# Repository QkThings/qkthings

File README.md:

Welcome to QkThings!
=====================

The open source framework and modular platform for smart devices.

**IMPORTANT:** read the [Building Instructions](http://discourse.qkthings.com/t/building-instructions/20) before cloning this repository.

Questions? Bugs? Visit [community.qkthings.com](http://community.qkthings.com) or send an email to `hello@qkthings.com`

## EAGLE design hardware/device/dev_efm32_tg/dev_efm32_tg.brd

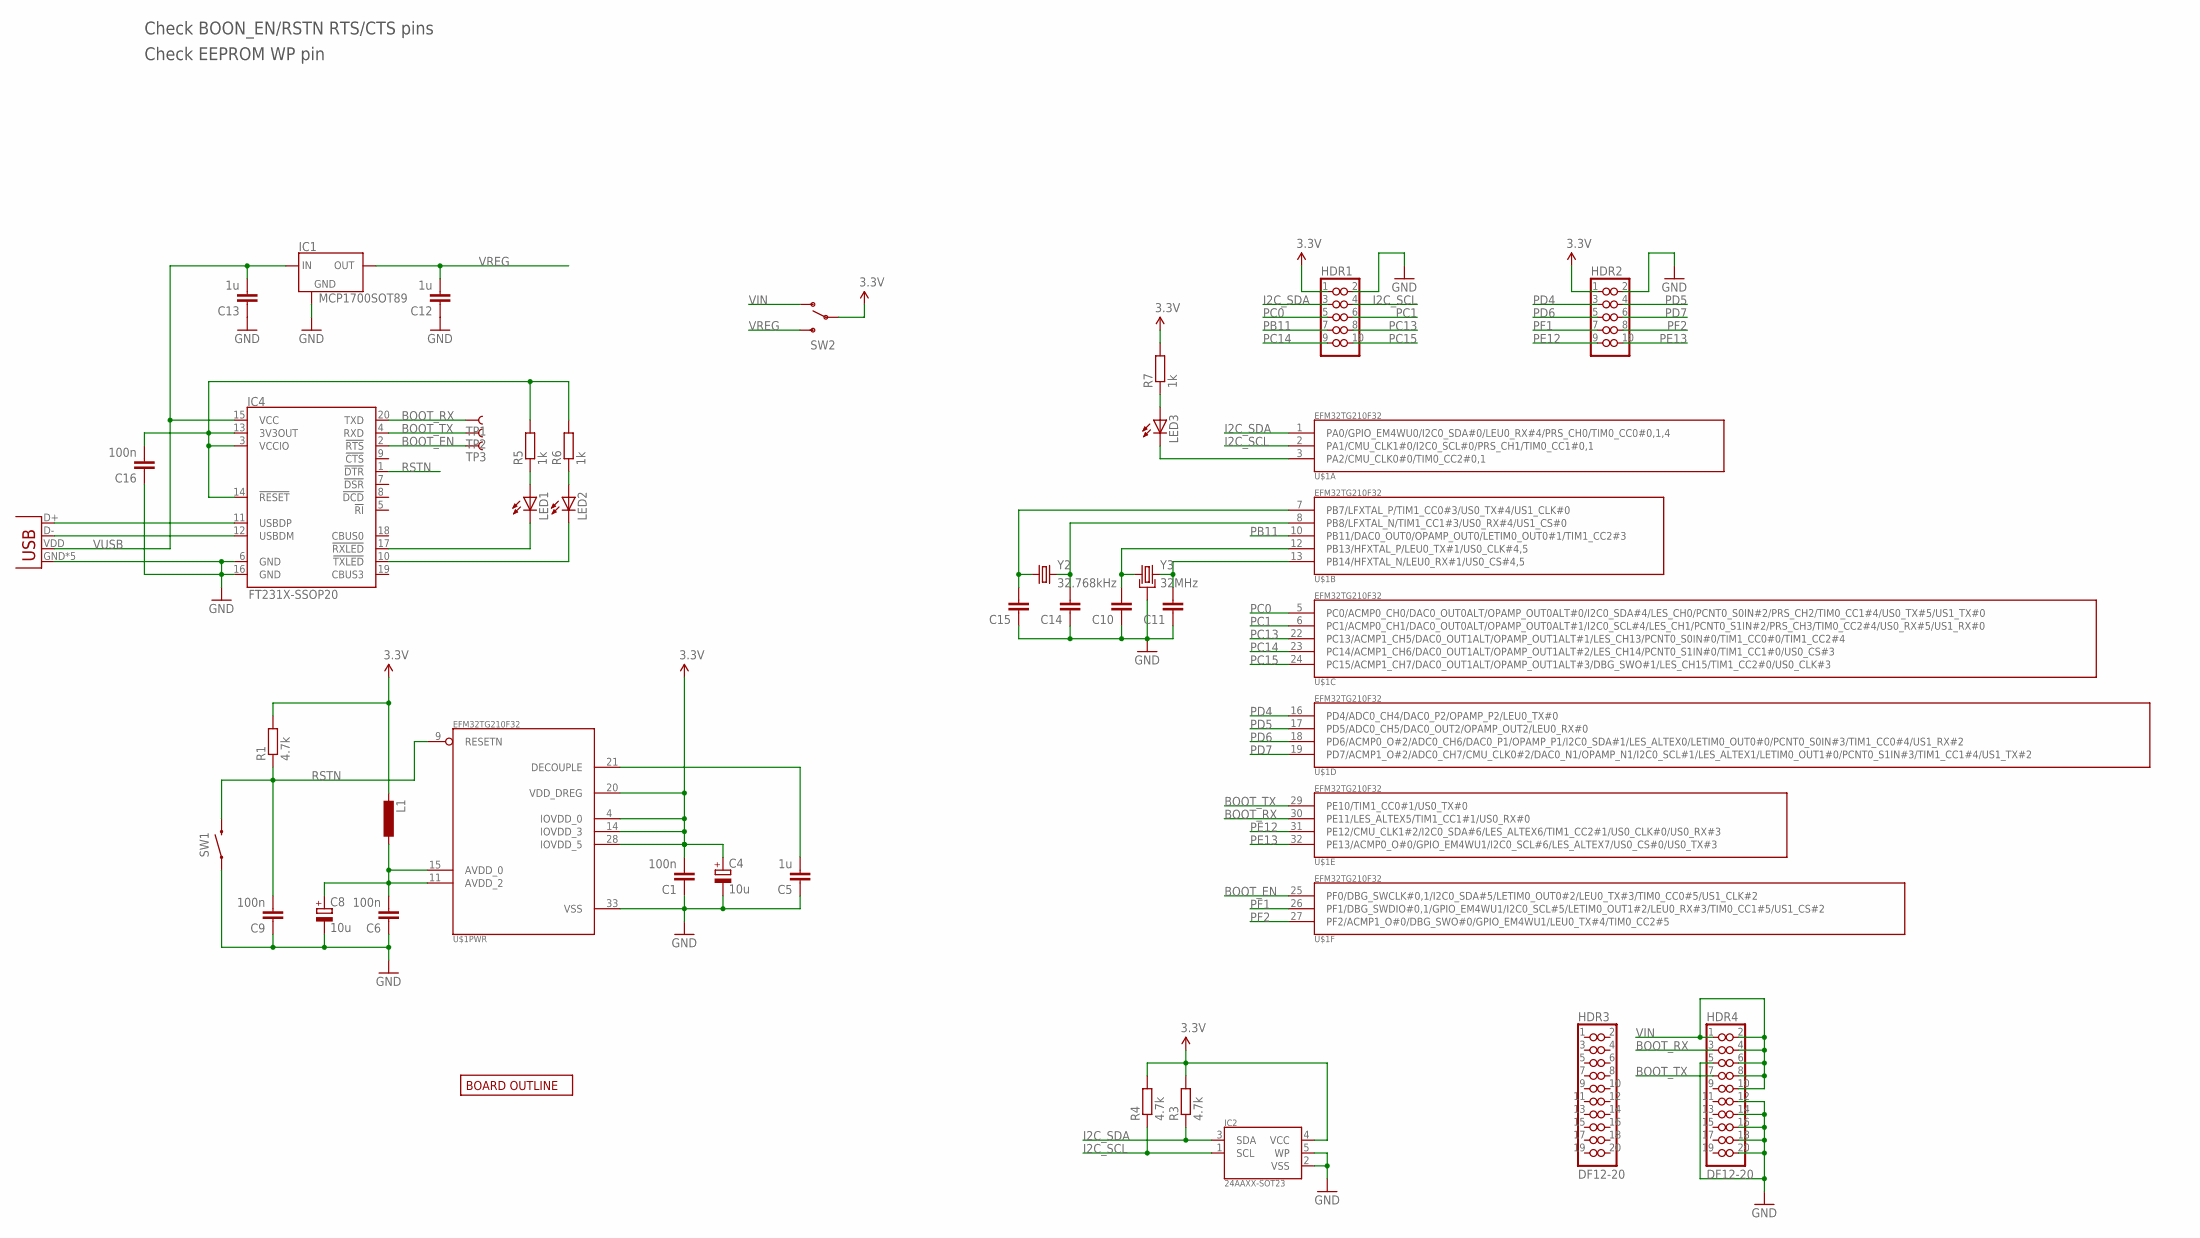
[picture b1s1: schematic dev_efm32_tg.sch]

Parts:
C1, C6, C9, C16: 100n; 0402
C4, C8: 10u; CAP_CASE_A
C5, C12, C13: 1u; 0402
C10, C11, C14, C15: C-0402; 0402
HDR1, HDR2: HDR2X05-ROUND; 2X05ROUND
HDR3, HDR4: DF12-20; DF12_20_MF
IC1: MCP1700SOT89; SOT89
IC2: 24AAXX-SOT23; SOT23-5
IC4: FT231X-SSOP20; SSOP20
L1: L-0402; 0402
LED1, LED2, LED3: LED0603; LED-0603
R1, R3, R4: 4.7k; 0402
R5, R6, R7: 1k; 0402
SW1: SWITCH_TACTILE-B3U-1000P; B3U-1000P
SW2: SWITCH_SPDT-PCM; PCM12SMTR
TP1, TP2, TP3: TP_1X1-1; TP_1X1_1
U$1: EFM32TG210F32; QFN32
U$2: USB-MICRO; 10118194_0001LF
U$3: QK-OUTLINE
Y2: 32.768kHz; ABS07
Y3: 32MHz; ABM8G

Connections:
3.3V: C1.2, C4.1 (+), HDR1.1, HDR2.1, IC2.4 (VCC), L1.2, R1.2, R3.2, R4.2, R7.2, SW2.2 (COM), U$1.4 (IOVDD_0), U$1.14 (IOVDD_3), U$1.20 (VDD_DREG), U$1.28 (IOVDD_5)
AVDD: C6.2, C8.1 (+), L1.1, U$1.11 (AVDD_2), U$1.15 (AVDD_0)
BOOT_EN: IC4.2 (!RTS), TP3.P$1, U$1.25 (PF0/DBG_SWCLK#0,1/I2C0_SDA#5/LETIM0_OUT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)
BOOT_RX: HDR4.3, IC4.20 (TXD), TP1.P$1, U$1.30 (PE11/LES_ALTEX5/TIM1_CC1#1/US0_RX#0)
BOOT_TX: HDR4.7, IC4.4 (RXD), TP2.P$1, U$1.29 (PE10/TIM1_CC0#1/US0_TX#0)
GND: C1.1, C4.2 (-), C5.1, C6.1, C8.2 (-), C9.1, C10.1, C11.1, C12.1, C13.1, C14.1, C15.1, C16.1, HDR1.2, HDR2.2, HDR4.5, HDR4.12, HDR4.14, HDR4.16, HDR4.18, HDR4.20, IC1.1 (GND), IC2.2 (VSS), IC2.5 (WP), IC4.6 (GND), IC4.16 (GND), SW1.P$1 (1), U$1.33 (VSS), U$2.GND, U$2.PAD1 (GND), U$2.PAD2 (GND), U$2.SHIELD1 (GND), U$2.SHIELD2 (GND), Y3.2 (SHIELD), Y3.4 (SHIELD)
I2C_SCL: HDR1.4, IC2.1 (SCL), R4.1, U$1.2 (PA1/CMU_CLK1#0/I2C0_SCL#0/PRS_CH1/TIM0_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)
I2C_SDA: HDR1.3, IC2.3 (SDA), R3.1, U$1.1 (PA0/GPIO_EM4WU0/I2C0_SDA#0/LEU0_RX#4/PR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)
unnamed: C5.2, U$1.21 (DECOUPLE)
unnamed: C11.2, U$1.13 (PB14/HFXTAL_N/LEU0_RX#1/US0_CS#4,5), Y3.3 (2)
unnamed: C14.2, U$1.8 (PB8/LFXTAL_N/TIM1_CC1#3/US0_RX#4/US1_CS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), Y2.P$2 (2)
unnamed: C10.2, U$1.12 (PB13/HFXTAL_P/LEU0_TX#1/US0_CLK#4,5), Y3.1
unnamed: C15.2, U$1.7 (PB7/LFXTAL_P/TIM1_CC0#3/US0_TX#4/US1_CL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), Y2.P$1 (1)
unnamed: IC4.11 (USBDP), U$2.D+
unnamed: IC4.12 (USBDM), U$2.D-
unnamed: LED1.A, R5.1
unnamed: LED2.A, R6.1
unnamed: IC4.17 (!RXLED), LED1.C
unnamed: IC4.10 (!TXLED), LED2.C
unnamed: LED3.A, R7.1
unnamed: LED3.C, U$1.3 (PA2/CMU_CLK0#0/TIM0_CC2#0,1)
unnamed: C16.2, IC4.3 (VCCIO), IC4.13 (3V3OUT), IC4.14 (!RESET), R5.2, R6.2
PB11: HDR1.7, U$1.10 (PB11/DAC0_OUT0/OPAMP_OUT0/LETIM0_OUT0#1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)
PC0: HDR1.5, U$1.5 (PC0/ACMP0_CH0/DAC0_OUT0ALT/OPAMP_OUT0AL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)
PC1: HDR1.6, U$1.6 (PC1/ACMP0_CH1/DAC0_OUT0ALT/OPAMP_OUT0AL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)
PC13: HDR1.8, U$1.22 (PC13/ACMP1_CH5/DAC0_OUT1ALT/OPAMP_OUT1A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)
PC14: HDR1.9, U$1.23 (PC14/ACMP1_CH6/DAC0_OUT1ALT/OPAMP_OUT1A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)
PC15: HDR1.10, U$1.24 (PC15/ACMP1_CH7/DAC0_OUT1ALT/OPAMP_OUT1A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)
PD4: HDR2.3, U$1.16 (PD4/ADC0_CH4/DAC0_P2/OPAMP_P2/LEU0_TX#0)
PD5: HDR2.4, U$1.17 (PD5/ADC0_CH5/DAC0_OUT2/OPAMP_OUT2/LEU0_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)
PD6: HDR2.5, U$1.18 (PD6/ACMP0_O#2/ADC0_CH6/DAC0_P1/OPAMP_P1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)
PD7: HDR2.6, U$1.19 (PD7/ACMP1_O#2/ADC0_CH7/CMU_CLK0#2/DAC0_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)
PE12: HDR2.9, U$1.31 (PE12/CMU_CLK1#2/I2C0_SDA#6/LES_ALTEX6/T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)
PE13: HDR2.10, U$1.32 (PE13/ACMP0_O#0/GPIO_EM4WU1/I2C0_SCL#6/L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)
PF1: HDR2.7, U$1.26 (PF1/DBG_SWDIO#0,1/GPIO_EM4WU1/I2C0_SCL#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)
PF2: HDR2.8, U$1.27 (PF2/ACMP1_O#0/DBG_SWO#0/GPIO_EM4WU1/LEU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)
RSTN: C9.2, IC4.1 (!DTR), R1.1, SW1.P$2 (2), U$1.9 (RESETN)
VIN: HDR4.1, HDR4.2, HDR4.4, HDR4.6, HDR4.8, HDR4.10, SW2.1
VREG: C12.2, IC1.3 (OUT), SW2.3 (2)
VUSB: C13.2, IC1.2 (IN), IC1.4 (IN), IC4.15 (VCC), U$2.VDD (VBUS)

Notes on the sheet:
Check BOON_EN/RSTN RTS/CTS pins
Check EEPROM WP pin

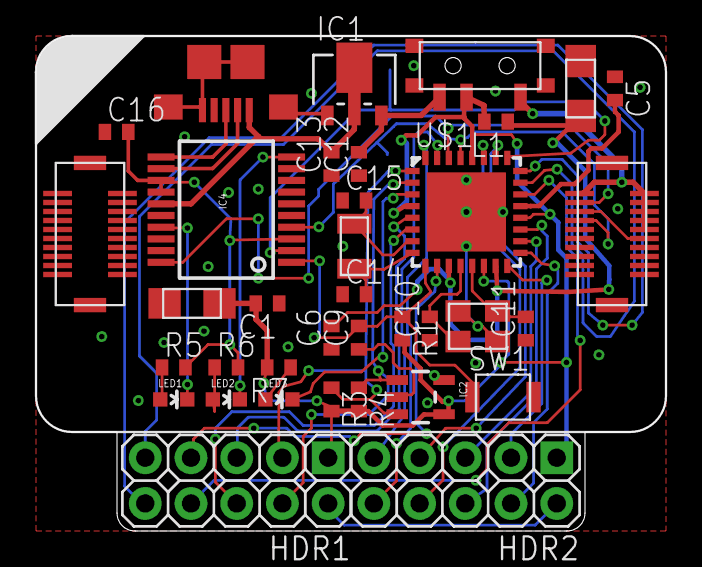
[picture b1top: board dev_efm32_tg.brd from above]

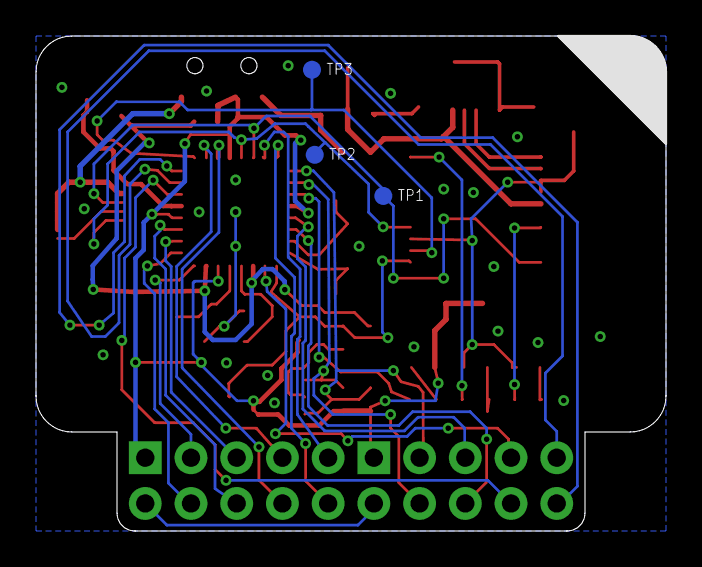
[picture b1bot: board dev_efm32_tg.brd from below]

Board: 2 copper layers, 35.0 x 27.5 mm, 40 parts (3 on the bottom side), 40 nets.

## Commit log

2013-12-01 readme added
2013-12-01 logo added
2013-12-02 readme updated
2013-12-08 deploy_embedded.py removed
2014-04-11 uptade
2014-04-12 bullet proof makefiles
2014-06-07 qkconnect deleted, qkutils update
2014-06-10 Embedded makefile updated
2014-08-01 Update. Moving to comm_bluetooth_2_0 and using QkPeripheral
2014-08-19 Update after release 20140819
2014-08-19 README edited
2014-08-19 Deprecated software installer removed.
2014-09-01 license.py removed
2014-09-07 chibios initial support added
2014-09-18 makefile updated
2014-10-05 Added Vagrant file
2014-10-10 vagrant: complete development environment (all repos and toolchains)
2014-10-11 toolman added, vagrant bootstrap.sh updated
2014-10-12 qkthings linux bootstrap added
2014-10-12 readme changed, vagrant not supported yet
2014-10-12 minor edits
2014-10-12 install opengl package
2014-10-12 git tools added to bootstrap, embedded deploy is now much less verbose
2014-10-15 install libusb-dev package
2014-10-16 qkthings_local folder added
2014-10-16 permissions added to toolchain dir
2014-10-16 permissions added at the end
2014-10-16 user can specify a different root dir
2014-10-17 bug fixed: ~ is not expanded on makefile
2014-11-14 python dev tools now have a setup.py
2014-11-14 toolman.py minor edit
2014-11-16 qkthings_linux_bootstrap.sh updated
2014-12-17 Deploy tools and script improved
2014-12-17 Directories organization
2014-12-17 References of software/ removed
2014-12-17 Deploy script improvements
2014-12-18 Python tools installed during bootstrap
2014-12-18 Bootstrap script is now a bash script, not shell
2014-12-18 Improvements on bootstrap
2014-12-18 Bootstrap improvements

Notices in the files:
parts and their libraries:
EnergyMicro: CC0 License
